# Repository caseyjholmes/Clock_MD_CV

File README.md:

# Clock_MD_CV
Modified 4HP 2 channel CV controlled clock multiplier and divider Eurorack Module originally by HAGIWO with PSI power and CV input modifications drawn onto PCB by:
HOLMES MODULAR 7-17-23

Just print a PCB, panel and assemeble acording to BOM. Then program with arduino IDE or atmel studio. 
Check back soon for a note here when the module has been tested and completed/finalized. 7-17-23

This module has been tested and completed. The updated firmware has also been posted. Youtube videos to be posted soon as well as Modular Grid data. 8-23-23
Update: Here's a youtube video showing the module purpose and operation. https://youtu.be/xJtNhXA8xrQ?si=LwXfrnCbjALYdgvX
Modular Grid link coming soon. 
Thanks Hagiwo! I hope my additions are pleasing. 

A BOM update has been added to reflect use of LM40405.0 reference shunt instead of lm40412. This change was a necessary correction due to using renamed component packages in eagle. 8-24-23
This change was also updated in the bottom bom CSV files and schematic.

View this module on Modular Grid
https://www.modulargrid.net/e/other-unknown-holmes-modular-clock-md-cv

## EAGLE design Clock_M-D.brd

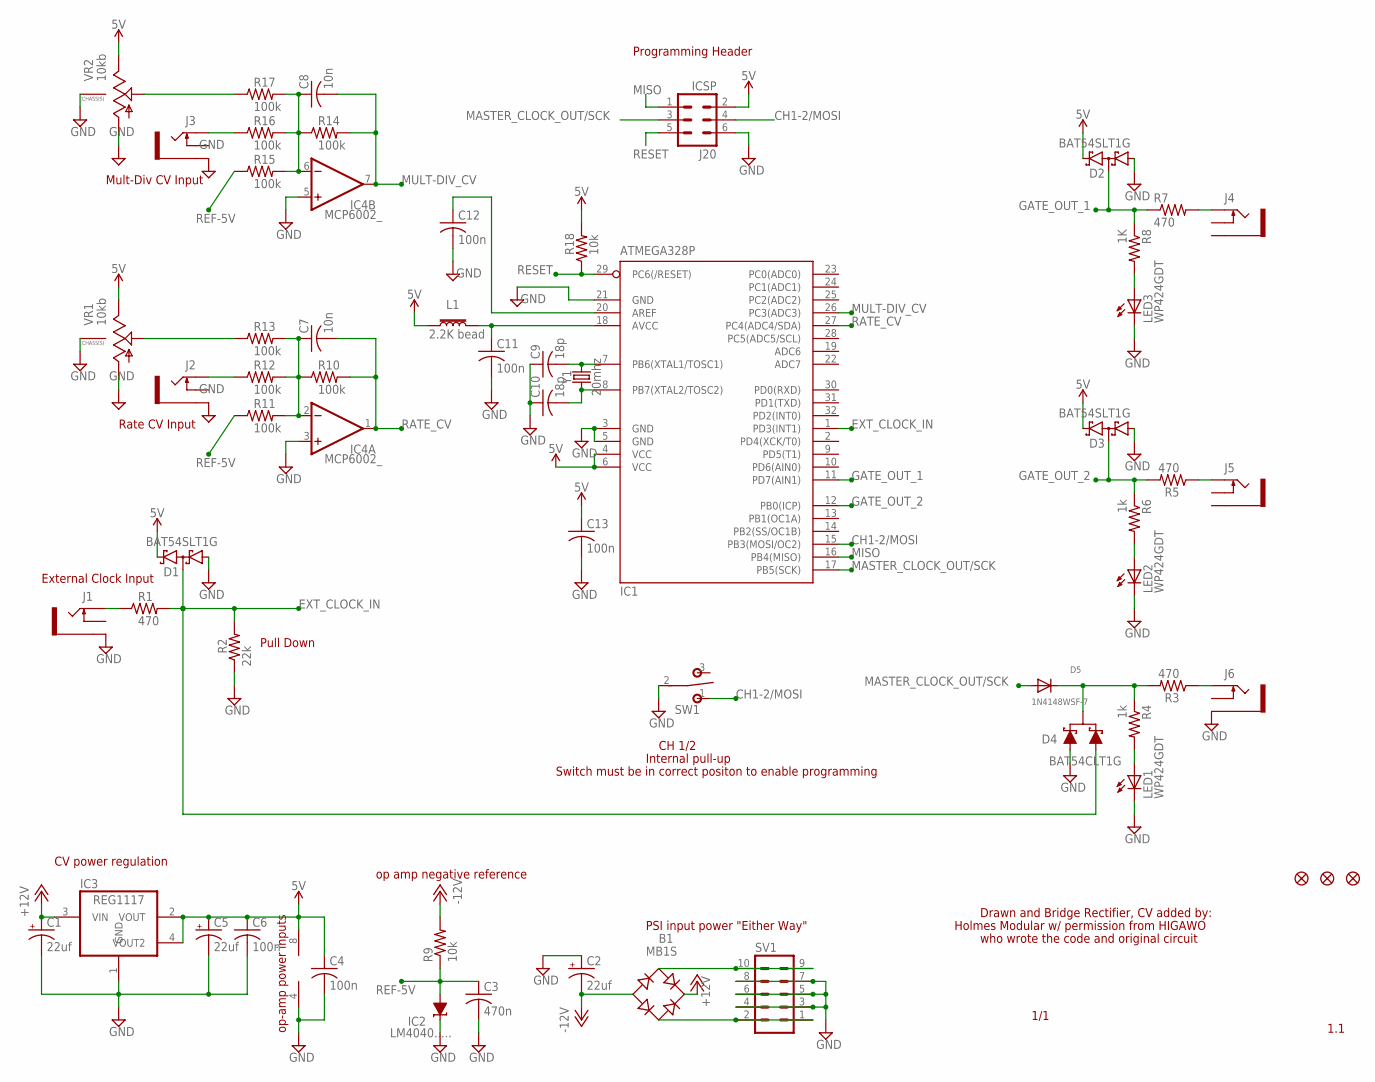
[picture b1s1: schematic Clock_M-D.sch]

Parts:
B1: MB1S; SOIC-4
C1, C2, C5: 22uf; PANASONIC_C
C3: 470n; C0805K
C4, C6, C11, C12, C13: 100n; C0805K
C7, C8: 10n; C0805K
C9, C10: 18p; C0805K
D1, D2, D3: BAT54SLT1G; SOT23
D4: BAT54CLT1G; SOT23-3
D5: 1N4148WSF-7; SOD-323F
FD1, FD2, FD3: FIDUCIAL1X2; FIDUCIAL-1X2
IC1: ATMEGA328P; TQFP32-08
IC2: LM4040.....; DBZ_R-PDSO-G3
IC3: REG1117; SOT223
IC4: MCP6002_; SO08
J1, J2, J3, J4, J5, J6: THONKICONNNEW; WQP-PJ301M-12_JACK
J20: ICSP; MA03-2
L1: 2.2K bead; 0603
LED1, LED2, LED3: WP424GDT; LED3MM
R1, R3, R5, R7: 470; R0805
R2: 22k; R0805
R4, R6: 1k; R0805
R8: 1K; R0805
R9, R18: 10k; R0805
R10, R11, R12, R13, R14, R15, R16, R17: 100k; R0805
SV1: EURO_POWER_HEADERLOCK; 10PIN_BACKSIDE
SW1: T-80-T-SPDT-ON-OFF-ON; M9040P
VR1, VR2: 10kb; 9MM_SNAP-IN_POT
Y1: 20mhz; CRYSTAL-SMD-5X3.2-2PAD

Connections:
5V: C4.1, C5.+, C6.1, C13.1, D1.2 (C2), D2.2 (C2), D3.2 (C2), IC1.4 (VCC), IC1.6 (VCC), IC3.2 (VOUT), IC3.4 (VOUT2), IC4.8 (V+), J20.2, L1.1, R18.2, VR1.3 (E), VR2.3 (E)
+12V: B1.+, C1.+, IC3.3 (VIN)
-12V: B1.-, C2.-, R9.2
CH1-2/MOSI: IC1.15 (PB3(MOSI/OC2)), J20.4, SW1.1 (O)
EXT_CLOCK_IN: D1.3 (C1A2), D4.2 (A1), IC1.1 (PD3(INT1)), R1.2, R2.2
GATE_OUT_1: D2.3 (C1A2), IC1.11 (PD7(AIN1)), R7.1, R8.1
GATE_OUT_2: D3.3 (C1A2), IC1.12 (PB0(ICP)), R5.2, R6.1
GND: C1.-, C2.+, C3.2, C4.2, C5.-, C6.2, C9.1, C10.1, C11.2, C12.2, C13.2, D1.1 (A1), D2.1 (A1), D3.1 (A1), D4.1 (A), IC1.3 (GND), IC1.5 (GND), IC1.21 (GND), IC2.1 (C), IC3.1 (GND), IC4.3 (+IN), IC4.4 (V-), IC4.5 (+IN), J1.P$3_SLEEVE (SLEEVE), J2.P$3_SLEEVE (SLEEVE), J3.P$3_SLEEVE (SLEEVE), J6.P$3_SLEEVE (SLEEVE), J20.6, LED1.K (C), LED2.K (C), LED3.K (C), R2.1, SV1.3, SV1.4, SV1.5, SV1.6, SV1.7, SV1.8, SW1.2, VR1.1 (A), VR1.CHASSIS1, VR1.CHASSIS2, VR2.1 (A), VR2.CHASSIS1, VR2.CHASSIS2
MASTER_CLOCK_OUT/SCK: D5.A, IC1.17 (PB5(SCK)), J20.3
MISO: IC1.16 (PB4(MISO)), J20.1
MULT-DIV_CV: C8.2, IC1.26 (PC3(ADC3)), IC4.7 (OUT), R14.2
unnamed: B1.~1 (AC1), SV1.9, SV1.10
unnamed: B1.~2 (AC2), SV1.1, SV1.2
unnamed: J1.P$1_TIP (TIP), R1.1
unnamed: D4.3 (C), D5.C, R3.2, R4.1
unnamed: LED1.A, R4.2
unnamed: J6.P$1_TIP (TIP), R3.1
unnamed: LED2.A, R6.2
unnamed: J5.P$1_TIP (TIP), R5.1
unnamed: J4.P$1_TIP (TIP), R7.2
unnamed: LED3.A, R8.2
unnamed: C7.1, IC4.2 (-IN), R10.1, R11.2, R12.2, R13.2
unnamed: J2.P$1_TIP (TIP), R12.1
unnamed: R13.1, VR1.2 (S)
unnamed: R17.1, VR2.2 (S)
unnamed: J3.P$1_TIP (TIP), R16.1
unnamed: C8.1, IC4.6 (-IN), R14.1, R15.2, R16.2, R17.2
unnamed: C11.1, IC1.18 (AVCC), L1.2
unnamed: C9.2, IC1.7 (PB6(XTAL1/TOSC1)), Y1.P$2 (2)
unnamed: C10.2, IC1.8 (PB7(XTAL2/TOSC2)), Y1.P$1 (1)
unnamed: C12.1, IC1.20 (AREF)
RATE_CV: C7.2, IC1.27 (PC4(ADC4/SDA)), IC4.1 (OUT), R10.2
REF-5V: C3.1, IC2.2 (A), R9.1, R11.1, R15.1
RESET: IC1.29 (PC6(/RESET)), J20.5, R18.1

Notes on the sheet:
CH 1/2
Internal pull-up
1/1
1.1
Holmes Modular w/ permission from HIGAWO
Drawn and Bridge Rectifier, CV added by:
who wrote the code and original circuit
op-amp power inputs
op amp negative reference
PSI input power "Either Way"
External Clock Input
CV power regulation
Rate CV Input
Mult-Div CV Input
Programming Header
Pull Down
Switch must be in correct positon to enable programming

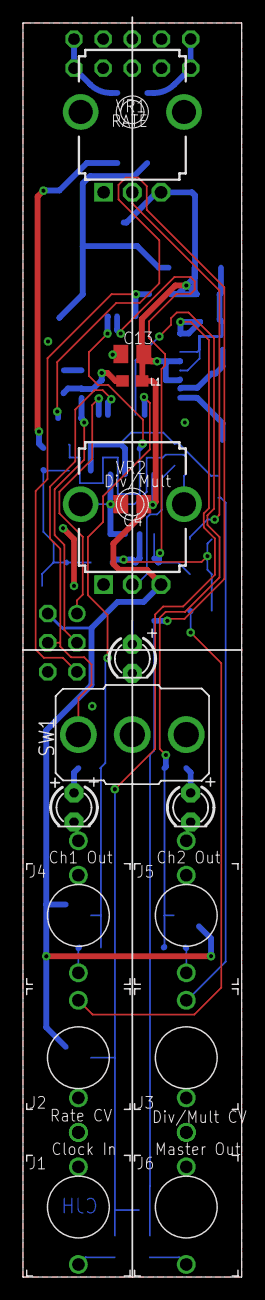
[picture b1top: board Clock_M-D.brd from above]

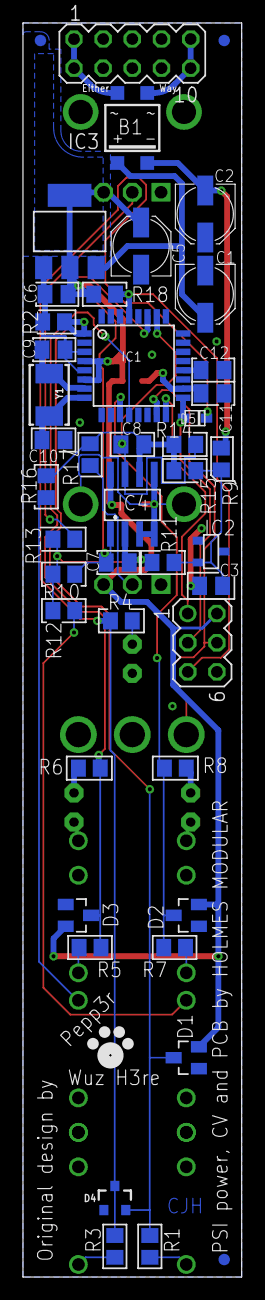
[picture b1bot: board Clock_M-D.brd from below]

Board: 2 copper layers, 19.1 x 109.2 mm, 60 parts (44 on the bottom side), 34 nets.

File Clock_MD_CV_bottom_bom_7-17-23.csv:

Comment,Designator,Footprint,LCSC Part #
1K,R8,R0805,
1N4148WSF-7,D5,SOD-323F,
1k,R4 R6,R0805,
10k,R9 R18,R0805,
10n,C7 C8,C0805K,
18p,C9 C10,C0805K,
20mhz,Y1,CRYSTAL-SMD-5X3.2-2PAD,
22k,R2,R0805,
22uf,C1 C2 C5,PANASONIC_C,
100k,R10 R11 R12 R13 R14 R15 R16 R17,R0805,
100n,C6 C11 C12,C0805K,
470,R1 R3 R5 R7,R0805,
470n,C3,C0805K,
ATMEGA328P,IC1,TQFP32-08,
BAT54CLT1G,D4,SOT23-3,
BAT54SLT1G,D1 D2 D3,SOT23,
FIDUCIAL1X2,FD1 FD2 FD3,FIDUCIAL-1X2,
LM4040.....,IC2,DBZ_R-PDSO-G3,
MB1S,B1,SOIC-4,
MCP6002_,IC4,SO08,
REG1117,IC3,SOT223,

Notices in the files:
parts and their libraries:
SparkFun-DiscreteSemi: Licensing: Creative Commons ShareAlike 4.0 International - https://creativecommons.org/licenses/by-sa/4.0
